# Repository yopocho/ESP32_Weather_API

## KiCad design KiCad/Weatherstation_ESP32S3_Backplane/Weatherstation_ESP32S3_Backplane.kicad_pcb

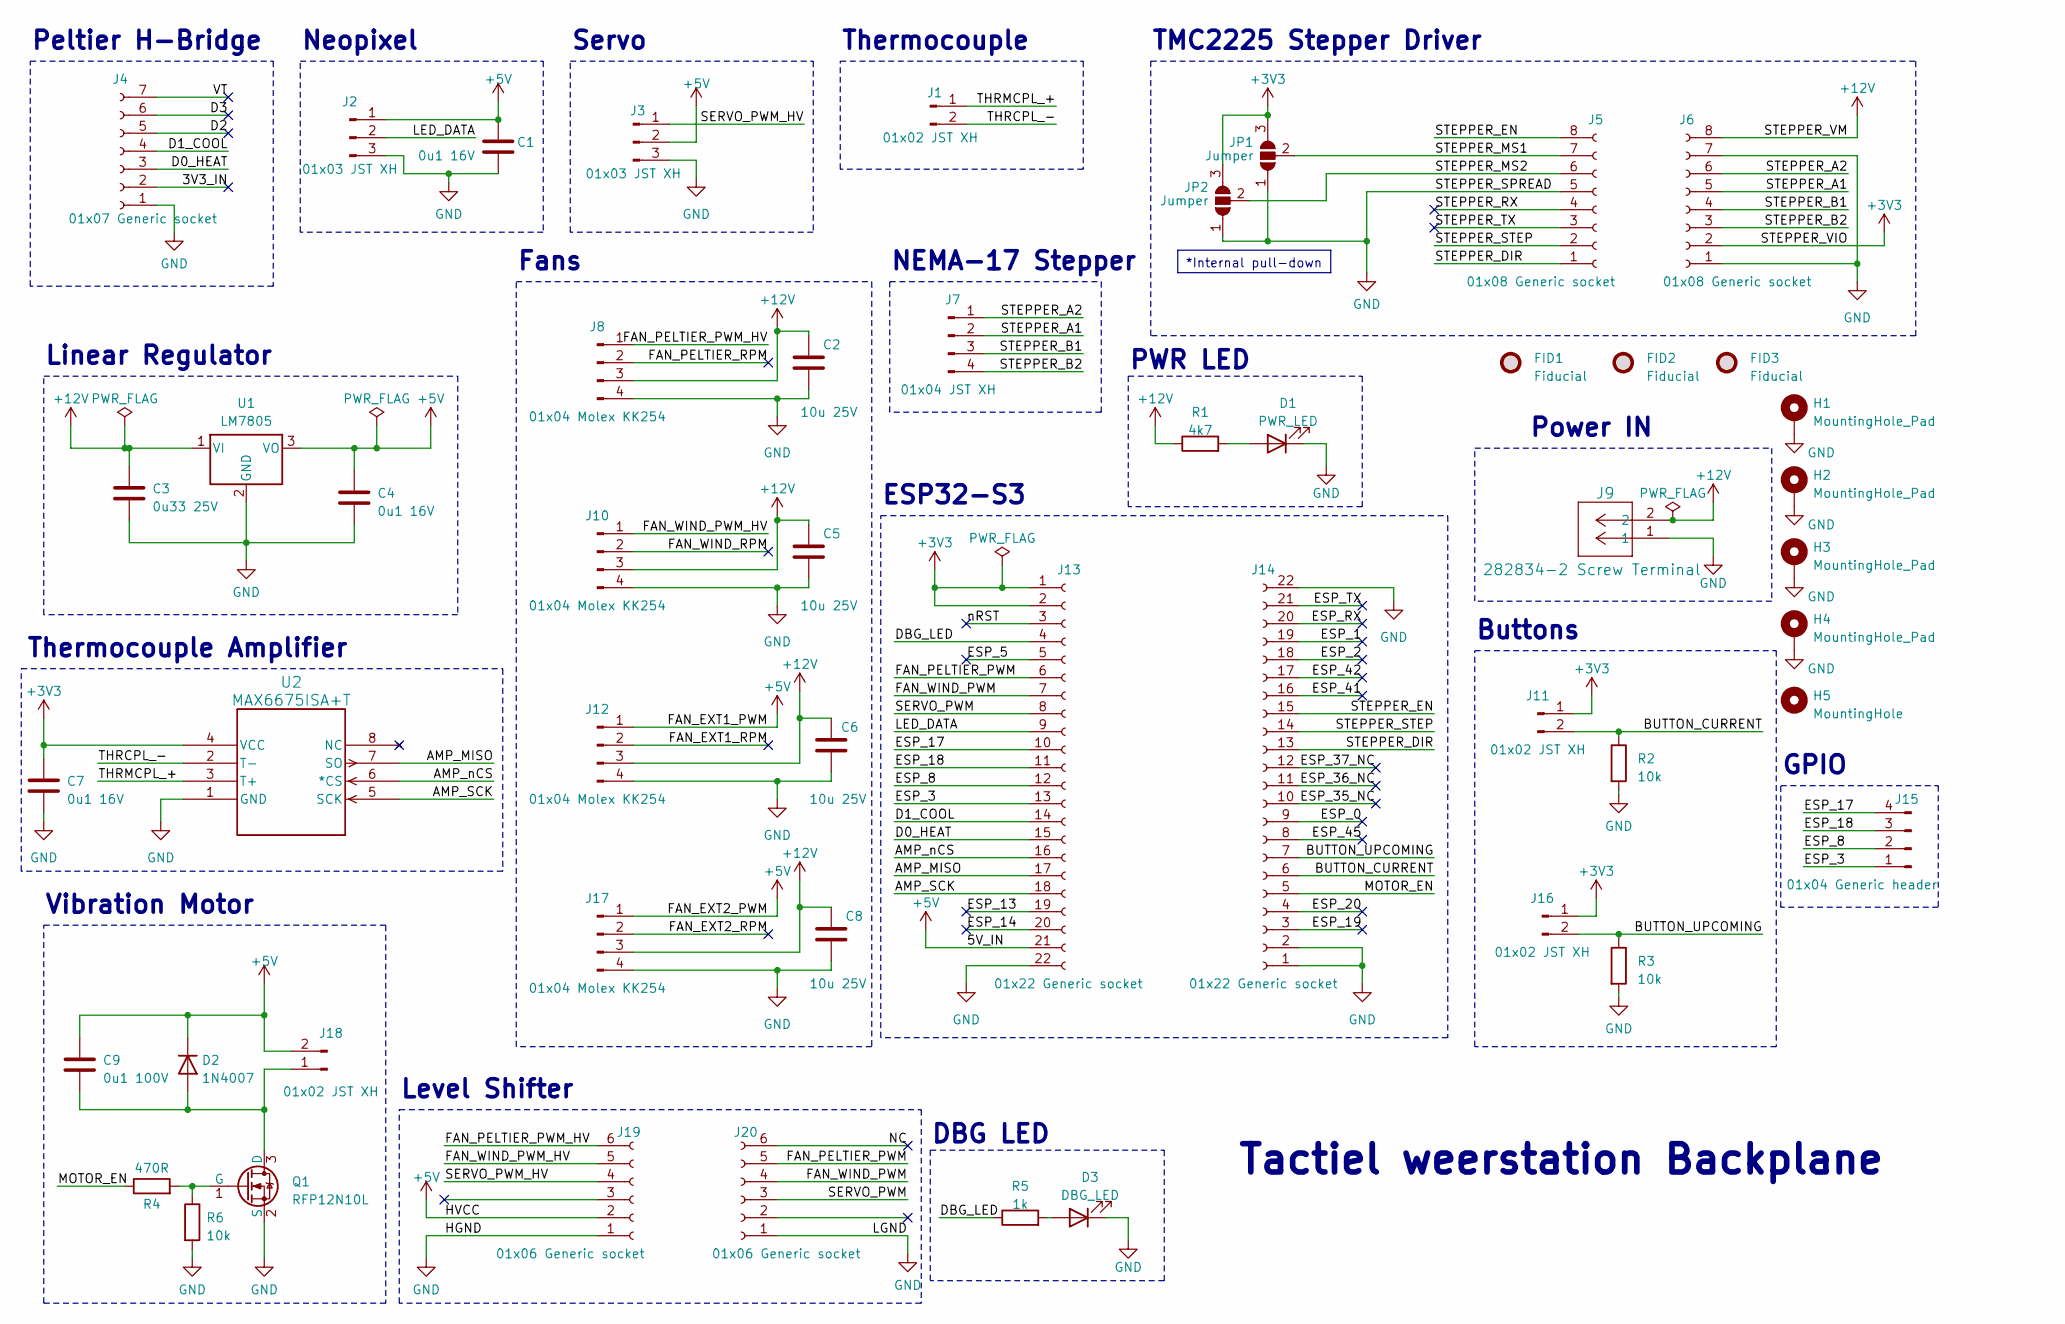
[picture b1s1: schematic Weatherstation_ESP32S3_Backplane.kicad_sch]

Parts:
C1, C4, C7: 0u1 16V; C_0402_1005Metric; LCSC Part # C1525
C2, C5, C6, C8: 10u 25V; C_1206_3216Metric; LCSC Part # C15850
C3: 0u33 25V; C_1206_3216Metric; LCSC Part # C1525
C9: 0u1 100V; C_0805_2012Metric; LCSC Part # C28233
D1: PWR_LED; LED_0805_2012Metric; LCSC Part # C84256
D2: 1N4007; D_DO-41_SOD81_P10.16mm_Horizontal
D3: DBG_LED; LED_0805_2012Metric; LCSC Part # C84256
FID1, FID2, FID3: Fiducial; Fiducial_1.5mm_Mask3mm
H1, H2, H3, H4: MountingHole_Pad; MountingHole_3.2mm_M3_Pad_Via
H5: MountingHole; MountingHole_2.2mm_M2
J1, J11, J16, J18: 01x02 JST XH; JST_XH_B2B-XH-A_1x02_P2.50mm_Vertical
J2, J3: 01x03 JST XH; JST_XH_B3B-XH-A_1x03_P2.50mm_Vertical
J4: 01x07 Generic socket; PinSocket_1x07_P2.54mm_Vertical
J5, J6: 01x08 Generic socket; PinSocket_1x08_P2.54mm_Vertical
J7: 01x04 JST XH; JST_XH_B4B-XH-A_1x04_P2.50mm_Vertical
J8, J10, J12, J17: 01x04 Molex KK254; Molex_KK-254_AE-6410-04A_1x04_P2.54mm_Vertical
J9: 282834-2 Screw Terminal; TerminalBlock_TE_282834-2_1x02_P2.54mm_Horizontal
J13, J14: 01x22 Generic socket; PinSocket_1x22_P2.54mm_Vertical
J15: 01x04 Generic header; PinHeader_1x04_P2.54mm_Vertical
J19, J20: 01x06 Generic socket; PinSocket_1x06_P2.54mm_Vertical
JP1, JP2: Jumper; SolderJumper-3_P2.0mm_Open_TrianglePad1.0x1.5mm
Q1: RFP12N10L; TO-220-3_Vertical
R1: 4k7; R_0805_2012Metric; LCSC Part # C17673
R2, R3, R6: 10k; R_0805_2012Metric; LCSC Part # C17414
R4: 470R; R_0805_2012Metric; LCSC Part # C17710
R5: 1k; R_0805_2012Metric; LCSC Part # C17673
U1: LM7805; TO-220-3_Horizontal_TabDown
U2: MAX6675ISA+T; SO-8_3.9x4.9mm_P1.27mm; LCSC Part # C16030

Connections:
+3V3: C7.2, J6.2, J11.1, J13.1, J13.2, J16.1, JP1.3 (B), JP2.3 (B), U2.4 (VCC)
+5V: C1.1, C4.1, C9.2, D2.1 (K), J2.1, J3.2, J12.1, J13.21, J17.1, J18.2, J19.2, U1.3 (VO)
+12V: C2.1, C3.1, C5.1, C6.1, C8.1, J6.8, J8.3, J9.2, J10.3, J12.3, J17.3, R1.1, U1.1 (VI)
/3V3_IN: J4.2
/AMP_MISO: J13.17, U2.7 (SO)
/AMP_SCK: J13.18, U2.5 (SCK)
/AMP_nCS: J13.16, U2.6 (*CS)
/BUTTON_CURRENT: J11.2, J14.6, R2.1
/BUTTON_UPCOMING: J14.7, J16.2, R3.1
/D0_HEAT: J4.3, J13.15
/D1_COOL: J4.4, J13.14
/D2: J4.5
/D3: J4.6
/DBG_LED: J13.4, R5.1
/ESP_0: J14.9
/ESP_1: J14.19
/ESP_2: J14.18
/ESP_3: J13.13, J15.1
/ESP_5: J13.5
/ESP_8: J13.12, J15.2
/ESP_13: J13.19
/ESP_14: J13.20
/ESP_17: J13.10, J15.4
/ESP_18: J13.11, J15.3
/ESP_19: J14.3
/ESP_20: J14.4
/ESP_35_NC: J14.10
/ESP_36_NC: J14.11
/ESP_37_NC: J14.12
/ESP_41: J14.16
/ESP_42: J14.17
/ESP_45: J14.8
/ESP_RX: J14.20
/ESP_TX: J14.21
/FAN_EXT1_RPM: J12.2
/FAN_EXT2_RPM: J17.2
/FAN_PELTIER_PWM: J13.6, J20.5
/FAN_PELTIER_PWM_HV: J8.1, J19.6
/FAN_PELTIER_RPM: J8.2
/FAN_WIND_PWM: J13.7, J20.4
/FAN_WIND_PWM_HV: J10.1, J19.5
/FAN_WIND_RPM: J10.2
/LED_DATA: J2.2, J13.9
/MOTOR_EN: J14.5, R4.1
/NC: J20.6
/SERVO_PWM: J13.8, J20.3
/SERVO_PWM_HV: J3.1, J19.4
/STEPPER_A1: J6.5, J7.2
/STEPPER_A2: J6.6, J7.1
/STEPPER_B1: J6.4, J7.3
/STEPPER_B2: J6.3, J7.4
/STEPPER_DIR: J5.1, J14.13
/STEPPER_EN: J5.8, J14.15
/STEPPER_MS1: J5.7, JP1.2 (C)
/STEPPER_MS2: J5.6, JP2.2 (C)
/STEPPER_RX: J5.4
/STEPPER_STEP: J5.2, J14.14
/STEPPER_TX: J5.3
/THRCPL_-: J1.2, U2.2 (T-)
/THRMCPL_+: J1.1, U2.3 (T+)
/VT: J4.7
/nRST: J13.3
unnamed: D1.2 (A), R1.2
unnamed: D3.2 (A), R5.2
unnamed: Q1.1 (G), R4.2, R6.1

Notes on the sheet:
*Internal pull-down
Vibration Motor
ESP32-S3
Linear Regulator
Tactiel weerstation Backplane
Peltier H-Bridge
PWR LED
Level Shifter
Neopixel
Fans
TMC2225 Stepper Driver
Power IN
Thermocouple
NEMA-17 Stepper
Servo
DBG LED
Buttons
Thermocouple Amplifier
GPIO

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
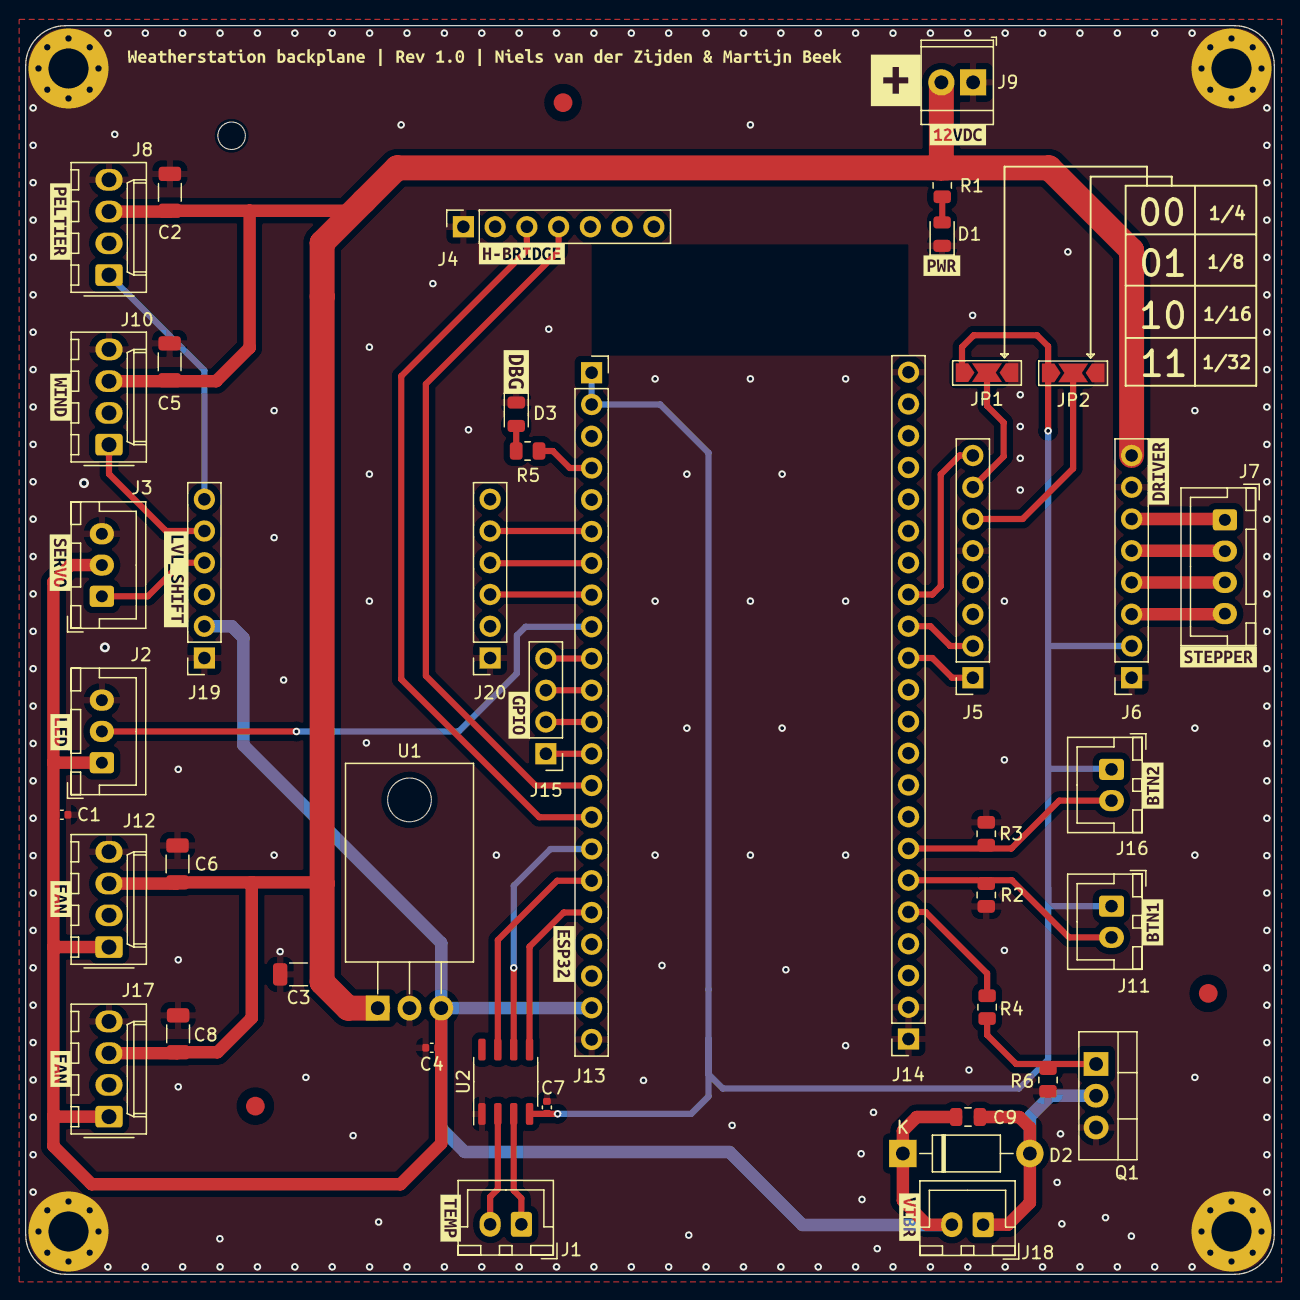
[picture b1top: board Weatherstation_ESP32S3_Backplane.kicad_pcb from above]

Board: 2 copper layers, 99.9 x 99.9 mm, 72 parts (0 on the bottom side), 39 nets.

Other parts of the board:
kibuzzard-643E6CEA: G***; kibuzzard-643E6CEA
kibuzzard-643E6CFB: G***; kibuzzard-643E6CFB
kibuzzard-643E6D8F: G***; kibuzzard-643E6D8F
kibuzzard-643E6D39: G***; kibuzzard-643E6D39
kibuzzard-643E6D96: G***; kibuzzard-643E6D96
kibuzzard-643E6DA6: G***; kibuzzard-643E6DA6
kibuzzard-643E6DC2: G***; kibuzzard-643E6DC2
kibuzzard-643FA2B4: G***; kibuzzard-643FA2B4
kibuzzard-6443C6BA: G***; kibuzzard-6443C6BA
kibuzzard-6443C6CC: G***; kibuzzard-6443C6CC
kibuzzard-6443C6EC: G***; kibuzzard-6443C6EC
kibuzzard-6443C8B0: G***; kibuzzard-6443C8B0
kibuzzard-6443C88F: G***; kibuzzard-6443C88F
kibuzzard-6443C714: G***; kibuzzard-6443C714
kibuzzard-6443CDE3: G***; kibuzzard-6443CDE3
kibuzzard-6443CE84: G***; kibuzzard-6443CE84
kibuzzard-6443DBAC: G***; kibuzzard-6443DBAC
kibuzzard-6443FD14: G***; kibuzzard-6443FD14
kibuzzard-6443FD19: G***; kibuzzard-6443FD19
kibuzzard-6446400D: G***; kibuzzard-6446400D
kibuzzard-6446408C: G***; kibuzzard-6446408C

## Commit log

2023-04-23 Tracking KiCad
2023-04-23 Added .README
2023-04-23 renamed: .README -> README.md
2023-04-23 Edited .gitignore
2023-04-23 modified: src/main.cpp [TEST COMMIT]
2023-04-23 modified: .gitignore, added KiCad stuff
2023-04-23 modified: src/main.cpp
2023-04-23 Edited 3D-model of ESP32 to better get a sense of the finished product
2023-04-23 Changed trackwidth of 3.3V to 1mm
2023-04-23 Changed the HU-logo from silkscreen to soldermask punch-out
2023-04-23 Moved HU-logo
2023-04-23 KiCad: Added origin for drill and placement files
2023-04-24 Moved from BS18D20 to MAX6675 thermocouple.
2023-04-24 Added DBG_LED, flat-mount LM7805, GPIO breakout header
2023-04-24 Finished PCB
2023-04-24 Generated production files
2023-04-24 Added the stepper code to core 0 (parallel process)
2023-04-24 Implemented proper xTask suspension during idle
2023-04-24 Added TODO list
2023-04-25 Condensed functions for extracting JSON values
2023-05-01 Added support for upcoming weather, added rain, snow and wind
2023-05-01 Mapped windspeed to fan PWM, added doOnceFlag for all weather besides temp
2023-05-01 Changed 3D-model of fan headers to represent correct part. Footprint & symbol needs to be changed at a later time/at the end to correct mistake made during design process.
2023-05-08 Added a buncha things
2023-05-08 Added neoPixel lib and logic
2023-05-30 Did too much too explain..
2023-06-06 Alles werkt, enkel nog QOL verbeteringen nodig!
2023-06-20 Added QoL and stability features
2023-06-26 Voor Martijn
2023-06-26 Please be the final fix, MARTIJN
2023-06-26 Added an if else to the training w/ no internet
2023-06-26 Removed an if-check to make the feedback motor work again -_-
2023-06-29 Fixed known issues with PCB: Connected neopixel directly to ESP32, not through level shifter; Exchanged drain & source of vibration motor MOSFET; Added 0,33uF MLCC between pin 1 and gnd of LM7805;
2023-07-12 FINAL commit; Everything stable and lovely
